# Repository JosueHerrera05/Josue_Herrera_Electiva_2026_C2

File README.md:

# Josue_Herrera_Electica_2026_C2
Repositorio Electíva Diseño Mecatrónico 2026-C2 
# PLC4UNI - Modelo NIVARA GC1

**PLC4UNI** es un Controlador Lógico Programable (PLC) modular, de código abierto y diseño robusto, creado específicamente como una plataforma didáctica para la enseñanza de mecatrónica y automatización. 

Este proyecto permite a los estudiantes interactuar con circuitos industriales reales manteniendo la seguridad del núcleo de procesamiento mediante aislamiento optoacoplado. El sistema está basado en el microcontrolador ESP32-S3.

## ¿En qué consiste el proyecto?
El proyecto abarca todo el ciclo de desarrollo de producto (basado en la norma IEEE-830 STD), incluyendo:
*   **Diseño Electrónico:** Esquemáticos y placa de circuito impreso (PCB) con entradas aisladas (24V DC), salidas a transistores de potencia/relé y puertos analógicos protegidos.
*   **Diseño Mecánico:** Carcasas personalizadas (superior e inferior) optimizadas para manufactura local mediante impresión 3D.
*   **Firmware/Software:** Código base de control que opera mediante un *Scan Cycle* de lazo cerrado (menor a 10ms) para garantizar el determinismo en tiempo real durante las prácticas.

## Programas Utilizados
Para visualizar, editar o compilar los archivos de este repositorio, se utilizaron las siguientes herramientas:
*   **[KiCad](https://www.kicad.org/):** Para el diseño esquemático, enrutamiento de la PCB y visualización 3D electrónica (`.kicad_sch`, `.kicad_pcb`).
*   **[FreeCAD](https://www.freecadweb.org/):** Para el diseño mecánico y modelado tridimensional de las carcasas (`.FCStd`).
*   **[Arduino IDE](https://www.arduino.cc/en/software) / [PlatformIO](https://platformio.org/):** Entornos de desarrollo para la programación del firmware en C/C++.
*   **Git:** Para el control de versiones de todo el proyecto.

## ¿Qué necesitas descargar e instalar?
Para trabajar con este proyecto en tu propia máquina, sigue estos pasos:

### 1. Clonar el repositorio
```bash
git clone https://github.com/JosueHerrera05/Josue_Herrera_Electica_2026_C2.git
```

### 2. Software Requerido
*   Instala **KiCad** (versión 7 o superior recomendada) si deseas editar las pistas, modificar los esquemas eléctricos o ver los modelos 3D de la placa.
*   Instala **FreeCAD** si necesitas modificar el diseño del chasis para ajustarlo a tu impresora 3D.
*   Instala el entorno de programación de tu preferencia (**Arduino IDE** o VSCode + **PlatformIO**) para cargar programas al PLC.

### 3. Dependencias de Hardware (Drivers y Librerías)
*   **Controlador USB-Serial:** Descarga e instala los drivers CH340 o CP2102 (según el módulo puente utilizado en tu placa) para que tu PC reconozca el PLC al conectarlo por cable USB.
*   **Gestor de Tarjetas ESP32:** Si usas Arduino IDE, debes instalar el paquete de tarjetas de Espressif (*esp32 by Espressif Systems*) desde el Gestor de Tarjetas para poder compilar y subir código al procesador ESP32-S3-WROOM-1.

## Estructura del Repositorio
*   `/CAD/`: Archivos de diseño mecánico y modelado 3D para la carcasa (FreeCAD).
*   `/PLC Electiva/`: Archivos del proyecto electrónico (KiCad), incluyendo esquemáticos, footprints y PCB.
*   `/Documentacion/`: Ensayos, manuales, reglamentos de seguridad y el documento oficial de especificaciones de requisitos (IEEE-830).
*   `/PLC4UNI/`: Directorio que contiene datasheets, referencias y archivos complementarios para la manufactura.

## Autores
*   **Desarrollo, Programación y Diseño:** Josue Stalin Herrera Valdez
*   **Dirección de Proyecto:** Carlos Pichardo
*   **Institución:** Instituto Tecnológico de Las Américas (ITLA) - Tecnólogo en Mecatrónica

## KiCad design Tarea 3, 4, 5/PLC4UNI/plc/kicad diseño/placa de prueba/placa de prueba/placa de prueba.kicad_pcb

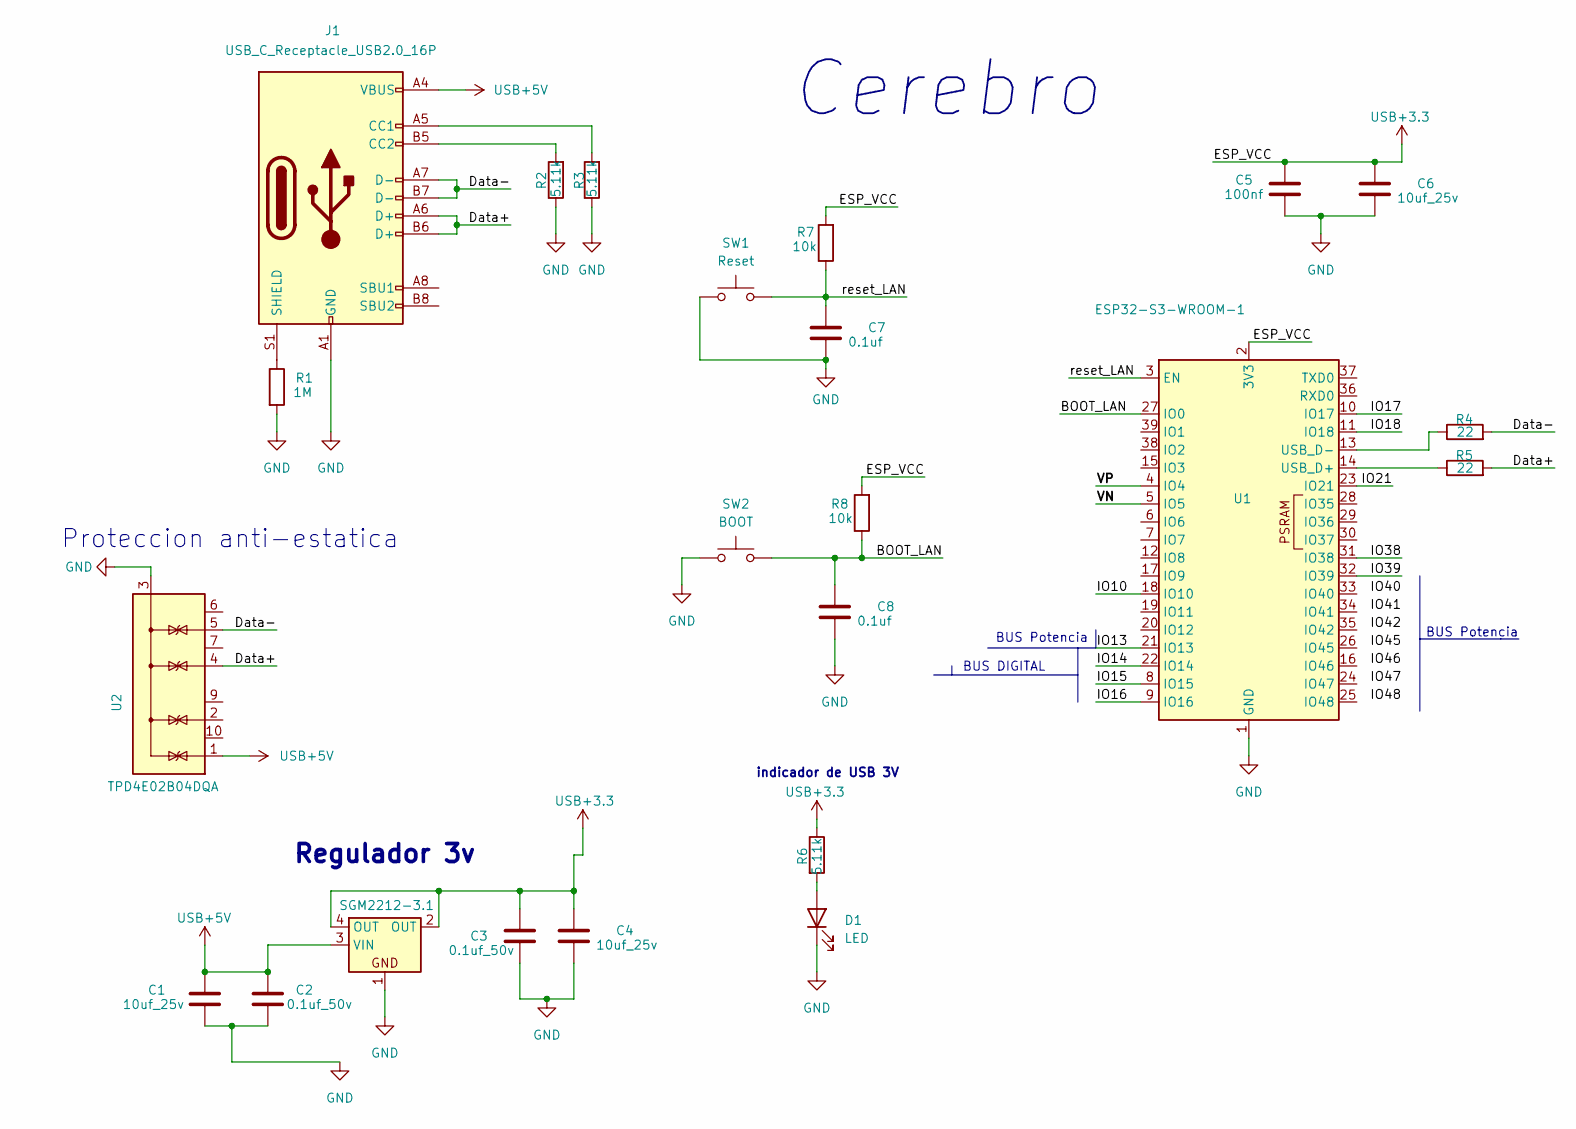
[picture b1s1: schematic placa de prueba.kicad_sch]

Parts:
C1, C4, C6: 10uf_25v; C_Disc_D4.7mm_W2.5mm_P5.00mm
C2, C3: 0.1uf_50v; C_Disc_D4.7mm_W2.5mm_P5.00mm
C5: 100nf; C_Disc_D4.7mm_W2.5mm_P5.00mm
C7, C8: 0.1uf; C_Disc_D4.7mm_W2.5mm_P5.00mm
D1: LED; LED_D1.8mm_W3.3mm_H2.4mm
J1: USB_C_Receptacle_USB2.0_16P; USB_C_Receptacle_GCT_USB4105-xx-A_16P_TopMnt_Horizontal
R1: 1M; R_Axial_DIN0414_L11.9mm_D4.5mm_P15.24mm_Horizontal
R2, R3, R6: 5.11k; R_Axial_DIN0414_L11.9mm_D4.5mm_P15.24mm_Horizontal
R4, R5: 22; R_Axial_DIN0414_L11.9mm_D4.5mm_P15.24mm_Horizontal
R7, R8: 10k; R_Axial_DIN0414_L11.9mm_D4.5mm_P15.24mm_Horizontal
SGM2212-3.1: SOT-223
SW1: Reset; SW_PUSH_6mm_H5mm
SW2: BOOT; SW_PUSH_6mm_H5mm
U1: ESP32-S3-WROOM-1
U2: TPD4E02B04DQA; USON-10_2.5x1.0mm_P0.5mm

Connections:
/BOOT_LAN: C8.1, R8.1, SW2.2, U1.27 (IO0)
/Data+: J1.A6 (D+), J1.B6 (D+), R5.2, U2.4 (IO3)
/Data-: J1.A7 (D-), J1.B7 (D-), R4.2, U2.5 (IO4)
/IO10: U1.18 (IO10)
/IO13: U1.21 (IO13)
/IO14: U1.22 (IO14)
/IO15: U1.8 (IO15)
/IO16: U1.9 (IO16)
/IO17: U1.10 (IO17)
/IO18: U1.11 (IO18)
/IO21: U1.23 (IO21)
/IO38: U1.31 (IO38)
/IO39: U1.32 (IO39)
/VN: U1.5 (IO5)
/VP: U1.4 (IO4)
/reset_LAN: C7.1, R7.1, SW1.2, U1.3 (EN)
GND: C1.2, C2.2, C3.2, C4.2, C5.2, C6.2, C7.2, C8.2, D1.1 (K), J1.A1 (GND), J1.A12 (GND), J1.B1 (GND), J1.B12 (GND), R1.2, R2.1, R3.1, SGM2212-3.1.1, SW1.1, SW2.1, U1.1 (GND), U1.40 (GND), U1.41 (GND), U2.3 (G), U2.8 (G)
unnamed: D1.2 (A), R6.2
unnamed: J1.A5 (CC1), R3.2
unnamed: J1.B5 (CC2), R2.2
unnamed: J1.S1 (SHIELD), R1.1
unnamed: R5.1, U1.14 (USB_D+)
unnamed: R4.1, U1.13 (USB_D-)
USB+3.3: C3.1, C4.1, C5.1, C6.1, R6.1, R7.2, R8.2, SGM2212-3.1.2 (OUT), SGM2212-3.1.4 (OUT), U1.2 (3V3)
USB+5V: C1.1, C2.1, J1.A4 (VBUS), J1.A9 (VBUS), J1.B4 (VBUS), J1.B9 (VBUS), SGM2212-3.1.3 (VIN), U2.1 (IO1)

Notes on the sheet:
Proteccion anti-estatica
BUS DIGITAL
BUS Potencia
Cerebro
indicador de USB 3V
Regulador 3v

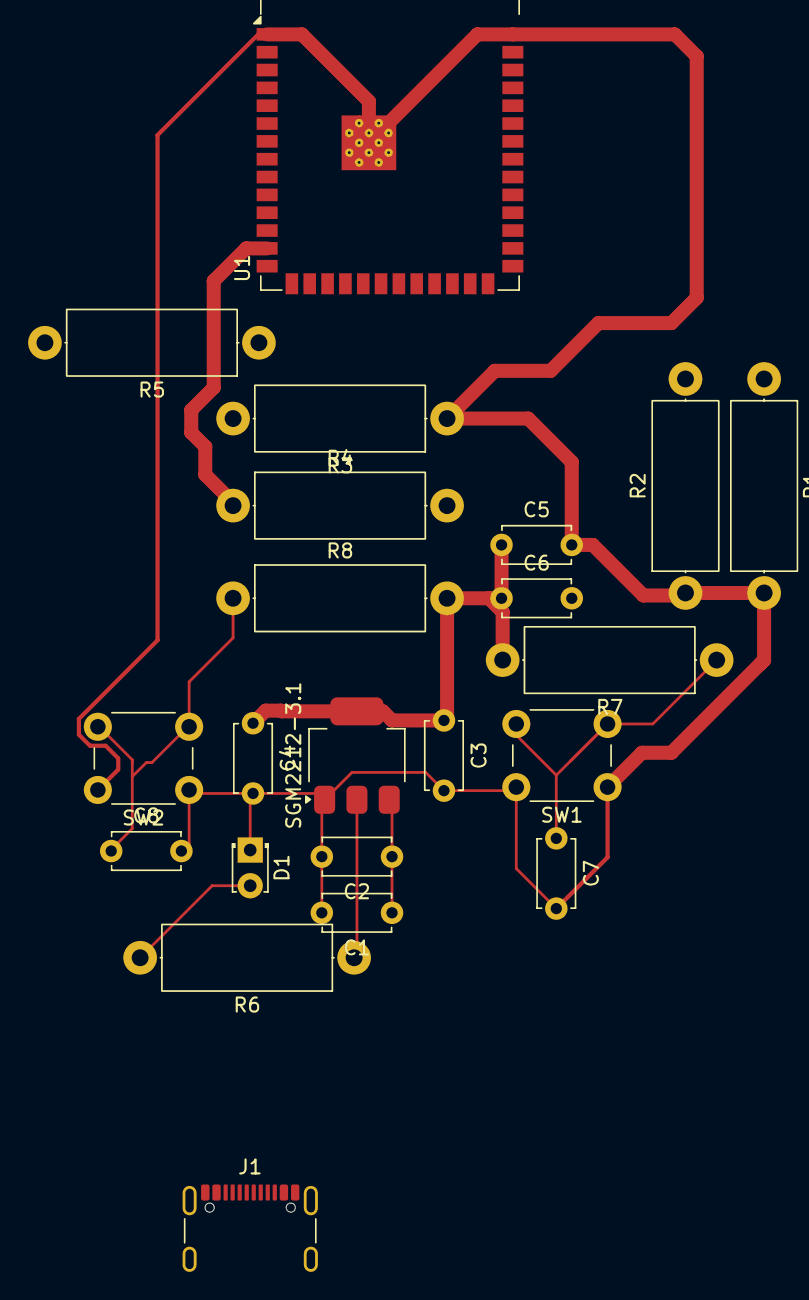
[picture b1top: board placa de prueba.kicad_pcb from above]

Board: 2 copper layers, 22 parts (0 on the bottom side), 13 nets.

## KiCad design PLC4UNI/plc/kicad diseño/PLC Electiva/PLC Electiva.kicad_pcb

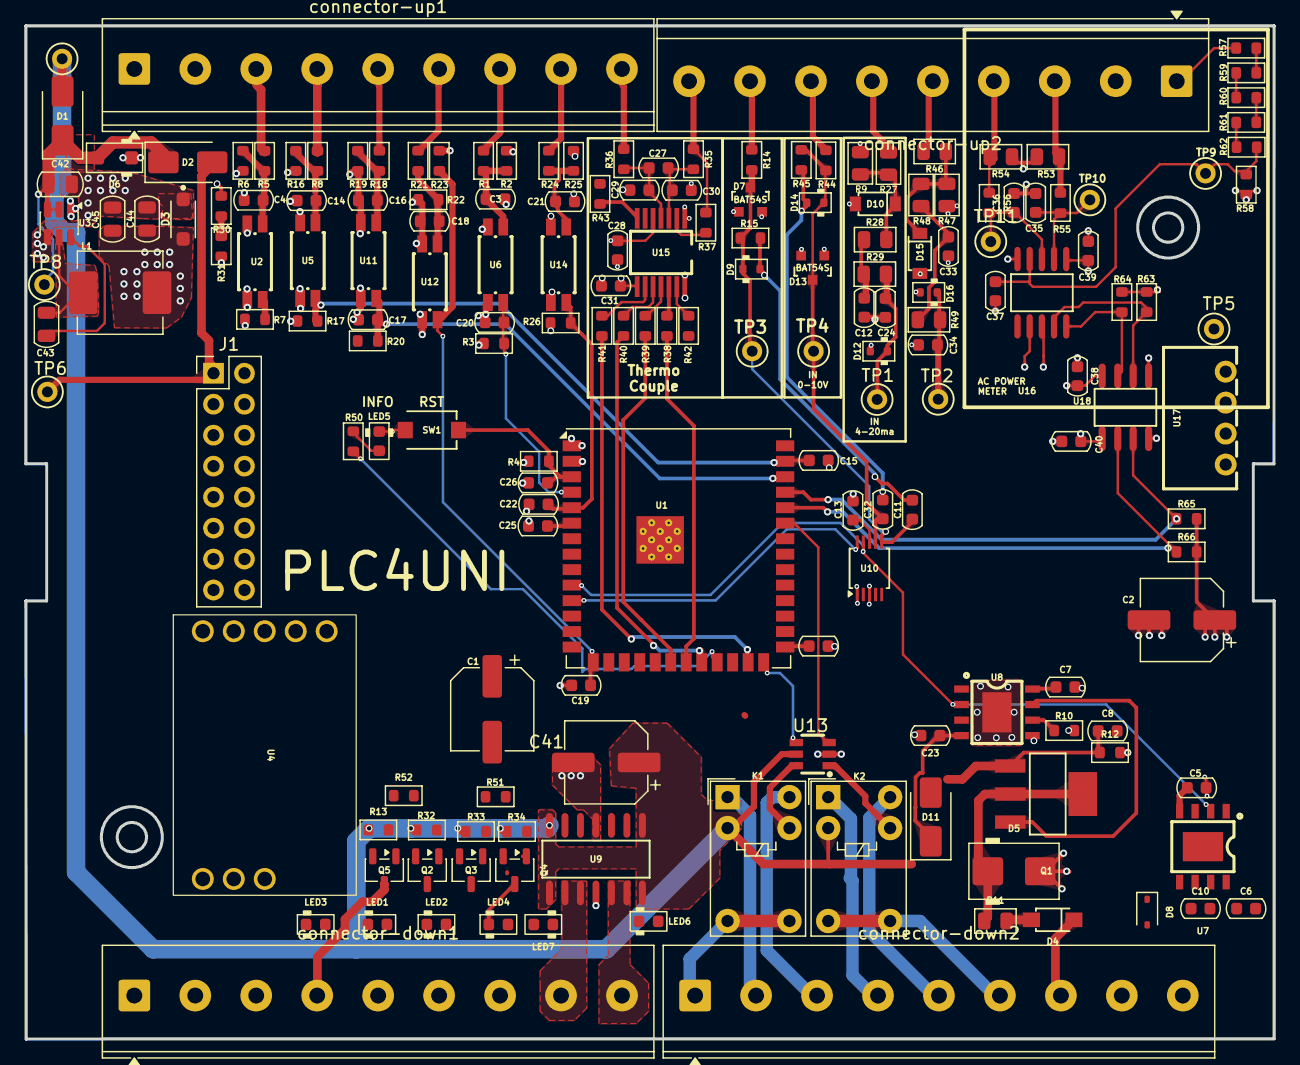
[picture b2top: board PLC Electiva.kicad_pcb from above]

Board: 2 copper layers, 102.4 x 83.1 mm, 177 parts (0 on the bottom side), 96 nets.

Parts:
C1, C2, C41: 47UF; CP_Elec_6.3x7.7
C3, C4, C14, C16, C18, C21: 2.2NF; C_0603_1608Metric
C5, C6, C7, C23: C_0603; C_0603_1608Metric
C8, C26: 1uF; C_0603_1608Metric
C9, C15, C17, C19, C20, C22: 1NF; C_0603_1608Metric
C10: 100nF; C_0603_1608Metric
C11, C12, C13, C28, C31, C32, C33, C38, C39, C40: 100NF; C_0603_1608Metric
C24, C34: 47PF; C_0603_1608Metric
C25: 100nf; C_0603_1608Metric
C27, C29, C30: 0.01UF; C_0603_1608Metric
C35, C36: 33NF; C_0603_1608Metric
C37: 68NF; C_0603_1608Metric
C42: 10uF; C_0805_2012Metric
C43: 100NF; C_0805_2012Metric
C44, C45: 22uF; C_0805_2012Metric
D1, D2: SS14; D_SMA
D3: SMF3.3; SMF3.3_SODFL3718X108N
D4: DSK120_C22466355; SOD-123FL_L2.7-W1.8-LS3.8-RD
D5: SMBJ28A; D_SMB
D6: SMF24CA; D_SOD-123F
D7, D13: BAT54S; SOT23-3_PO132
D8: SD12_SOD323; D_SOD-323
D9, D12, D14, D16: PESD5Z3.3; D_SOD-523
D10, D15: 1N5819HW-7-F; SOD-123_L2.7-W1.6-LS3.7-RD
D11: SMAJ12A; D_SMA
J1: Conn_02x08_Odd_Even; PinHeader_2x08_P2.54mm_Vertical
K1, K2: G5V-1; Relay_SPDT_Omron_G5V-1
L1: 10uH; L_APV_APH0630
LED1, LED2, LED3, LED4, LED5, LED6, LED7: LED_0603_Red; LED_0603_1608Metric
Q1: NCE60P04R; SOT-223-3_L6.5-W3.4-P2.30-LS7.0-BR
Q2, Q3, Q4, Q5: ZXMS6004FFQTA; SOT-23-3
R1, R5, R8, R18, R21, R24: 3.6K; R_0603_1608Metric
R2, R6, R16, R19, R22, R25: 3.3K; R_0603_1608Metric
R3, R4, R7, R17, R20, R23, R26: 22K; R_0603_1608Metric
R9, R47: 120R; R_0805_2012Metric
R10, R13, R30, R31, R32, R33, R34, R51, R52: R_0603; R_0603_1608Metric
R11: 15R; R_0805_2012Metric
R12: 470K; R_0603_1608Metric
R14, R44, R50: 2.2K; R_0603_1608Metric
R15, R45: 1.05K; R_0603_1608Metric
R27, R46: 49.9R; R_0805_2012Metric
R28, R48: 47K; R_0805_2012Metric
R29, R49: 100K; R_0805_2012Metric
R35, R36: 0R; R_0603_1608Metric
R37: 20K; R_0603_1608Metric
R38, R39, R40, R41, R42, R43: 150; R_0603_1608Metric
R53, R54: 0.51; R_0805_2012Metric
R55, R56: 1K; R_0603_1608Metric
R57, R59, R60, R61, R62: 390K; R_0603_1608Metric
R58: 510; R_0603_1608Metric
R63, R64, R65, R66: 4.7K; R_0603_1608Metric
SW1: TS-1088-AR02016; SW-SMD_L3.9-W3.0-P4.45
TP1, TP2, TP3, TP4, TP5, TP6, TP7, TP8, TP9, TP10, TP11: TestPoint_Hole1; TestPoint_WireHole
U1: ESP32-S3-WROOM-1; ESP32-S3-WROOM-1U
U2, U5, U6, U11, U12, U14: AT3H4B-CUH-S; SSOP-4_L2.7-W4.6-P1.27-LS7.0-TL
U3: AP63203WU; TSOT-23-6
U4: RS485-PROTECT; RS-485-PROTECT
U7: GP8211S-TC50-EW; ESOP-8_L4.9-W3.9-P1.27-LS6.0-BL-EP
U8: GP8302-TC50-EW; ESOP-8_L4.9-W3.9-P1.27-LS6.0-BL-EP
U9: BTS723GWXUMA1; SOIC-14_L8.7-W3.9-P1.27-LS6.0-BL
U10: ADS1115IDGS; TSSOP-10_3x3mm_P0.5mm
U13: LK1802; SOT-23-6_L2.9-W1.6-P0.95-LS2.8-BR
U15: MAX31856MUD+; TSSOP-14_L5.0-W4.4-P0.65-LS6.4-BL
U16: BL0942; SSOP-10_L4.9-W3.9-P1.00-LS6.0-BL
U17: B0303S-1WR3_C7465185; PWRM-TH_BXXXXS-1WR3
U18: ISO7021DR; SOIC-8_L4.9-W3.9-P1.27-LS6.0-BL
connector-down1, connector-down2: Screw_Terminal_9_P5.00mm; TerminalBlock_Phoenix_PT-1,5-9-5.0-H_1x09_P5.00mm_Horizontal
connector-up1, connector-up2: Screw_Terminal_9_P5.00mm; TerminalBlock_Phoenix_PT-1,5-9-5.0-H_1x09_P5.00mm_Horizontal

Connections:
+3.3V: C1.1, C2.1, C13.1, C28.1, C31.1, C40.2, C44.1, C45.1, D3.A, D7.2 (cathode), D13.2 (cathode), J1.2, L1.2, R3.2, R4.2, R7.2, R17.2, R20.2, R23.2, R26.2, R65.2, R66.2, U1.2 (3V3), U3.1 (FB), U4.1 (VCC), U9.11 (SPU), U10.8 (VDD), U15.5 (AVDD), U15.8 (DVDD), U17.2 (+Vin), U18.1 (VCC1)
+5V: D2.2 (A), J1.1, TP6.1 (1_1)
+24V: C4.2, C5.1, C14.2, C16.2, C18.2, C23.1, C41.1, D1.2 (A), D11.1 (A1), K1.2, K2.2, R6.1, R13.1, R16.1, R19.1, R22.1, R30.1, R32.1, R33.1, R34.1, TP7.1 (1_1), U2.2, U5.2, U7.4 (VCC), U8.4 (VCC), U9.1 (VBB), U9.7 (VBB), U9.8 (VBB), U9.14 (VBB), U11.2, U12.2, U13.5 (COM), connector-up1.9
/PowerSupply/sw: C43.2, L1.1, U3.5 (SW)
/PowerSupply/vdc_in: C42.1, D1.1 (K), D2.1 (K), D6.2 (A), TP8.1 (1_1), U3.2 (EN), U3.3 (IN)
/control/CON-IN_CT_N: R54.2, R56.1
/control/CON-IN_CT_P: R53.1, R55.1
/control/CON_IN_TC-: R35.1, R37.1
/control/CON_OUT_0-10V: C10.1, D8.2 (A2), U7.6 (VOUT)
/control/CON_OUT_NPN1: LED3.1 (K), Q5.3 (D)
/control/CON_OUT_NPN2: LED1.1 (K), Q2.3 (D)
/control/CON_OUT_NPN3: LED2.1 (K), Q3.3 (D)
/control/CON_OUT_NPN4: LED4.1 (K), Q4.3 (D)
/control/CON_OUT_PNP1: R51.1, U9.9 (OUT2), U9.10 (OUT2)
/control/CON_OUT_PNP2: R52.1, U9.12 (OUT1), U9.13 (OUT1)
/control/CON_OUT_RLY1_COM: K1.5, K1.6
/control/CON_OUT_RLY2_COM: K2.5, K2.6
/control/EMRX: R66.1, U1.36 (RXD0), U18.2 (OUTA)
/control/EM_TX: R65.1, U1.37 (TXD0), U18.3 (INB)
/control/EN: C26.2, R4.1, SW1.1, U1.3 (EN)
/control/IN-0-10V1/COM: C32.2, D14.2 (A), R45.2
/control/IN-0-10V1/OUT3V: C32.1, D13.3 (AK), D14.1 (K), R44.2, R45.1, TP4.1 (1_1), U10.7 (AIN3)
/control/IN-0-10V/COM: C11.2, D9.2 (A), R15.2
/control/IN-0-10V/OUT3V: C11.1, D7.3 (AK), D9.1 (K), R14.2, R15.1, TP3.1 (1_1), U10.6 (AIN2)
/control/IN-4-20MA1/OUT: C34.1, D16.1 (K), R49.1, TP2.1 (1_1), U10.5 (AIN1)
/control/IN-4-20MA/OUT: C24.1, D12.1 (K), R29.1, TP1.1 (1_1), U10.4 (AIN0)
/control/IN_NPN1: C9.1, R7.1, U1.27 (IO0), U2.4
/control/IN_NPN2: C15.1, R17.1, U1.39 (IO1), U5.4
/control/IN_NPN3: C17.1, R20.1, U1.38 (IO2), U11.4
/control/IN_NPN4: C19.1, R23.1, U1.15 (IO3), U12.4
/control/IN_PNP1: C20.1, R3.1, U1.4 (IO4), U6.4
/control/IN_PNP2: C22.1, R26.1, U1.5 (IO5), U14.4
/control/IN_VDC_ADC: C25.1, R30.2, R31.1, U1.6 (IO6)
/control/LED_INFO: R50.2, U1.23 (IO21)
/control/OUT_NPN1: Q5.1 (IN), U1.31 (IO38)
/control/OUT_NPN2: Q2.1 (IN), U1.32 (IO39)
/control/OUT_NPN3: Q3.1 (IN), U1.33 (IO40)
/control/OUT_NPN4: Q4.1 (IN), U1.34 (IO41)
/control/OUT_PNP1: U1.16 (IO46), U9.2 (IN1)
/control/OUT_PNP2: U1.24 (IO47), U9.6 (IN2)
/control/OUT_RLY1: U1.35 (IO42), U13.3 (1B)
/control/OUT_RLY2: U1.26 (IO45), U13.4 (2B)
/control/TEMP_CS: R41.2, U1.25 (IO48)
/control/clk: R40.2, U1.22 (IO14)
/control/i2c_scl: U1.11 (IO18), U7.1 (SCLK), U8.1 (SLCK), U10.10 (SCL)
/control/i2c_sda: U1.10 (IO17), U7.2 (SDA), U8.2 (SDA), U10.9 (SDA)
/control/miso: R39.2, U1.20 (IO12)
/control/mosi: R38.2, U1.21 (IO13)
Earth: C35.1, C36.2, C37.1, C38.1, C39.1, R53.2, R54.1, R58.1, U16.5 (GND), U16.7 (SEL), U17.3 (-Vout), U18.5 (GND2), connector-up2.2
GND: C1.2, C2.2, C3.2, C5.2, C6.2, C7.2, C8.2, C9.2, C10.2, C12.2, C13.2, C15.2, C17.2, C19.2, C20.2, C21.2, C22.2, C23.2, C24.2, C25.2, C26.1, C28.2, C29.2, C30.2, C31.2, C33.2, C34.2, C40.1, C41.2, C42.2, C44.2, C45.2, D3.C, D5.2 (A), D6.1 (K), D7.1 (Anode), D8.1 (A1), D10.2 (A), D12.2 (A), D13.1 (Anode), D15.2 (A), D16.2 (A), J1.15, J1.16, LED5.1 (K), LED6.1 (K), LED7.1 (K), Q2.2 (OUT), Q3.2 (OUT), Q4.2 (OUT), Q5.2 (OUT), R2.1, R9.1, R10.2, R12.2, R25.1, R31.2, R47.1, SW1.2, U1.1 (GND), U1.40 (GND), U1.41 (GND), U2.3, U3.4 (GND), U4.2 (GND), U5.3, U6.2, U6.3, U7.5 (GND), U7.9 (EP), U8.5 (GND), U8.9 (EP), U9.4 (GND), U10.1 (ADDR), U10.3 (GND), U11.3, U12.3, U13.2 (E), U14.2, U14.3, U15.1 (AGND), U15.14 (DGND), U17.1 (-Vin), U18.4 (GND1), connector-down2.9, connector-up1.8
unnamed: C3.1, R1.2, R2.2, U6.1
unnamed: C4.1, R5.2, R6.2, U2.1
unnamed: C12.1, R28.1, R29.2
unnamed: C14.1, R8.2, R16.2, U5.1
unnamed: C16.1, R18.2, R19.2, U11.1
unnamed: C18.1, R21.2, R22.2, U12.1
unnamed: C21.1, R24.2, R25.2, U14.1
unnamed: C33.1, R48.1, R49.2
unnamed: D4.2 (A), R11.2
unnamed: D5.1 (K), Q1.2, Q1.4, R11.1
unnamed: D10.1 (K), R9.2, R27.1, R28.2
unnamed: C8.1, D11.2 (A2), Q1.1, R12.1
unnamed: D15.1 (K), R46.1, R47.2, R48.2
unnamed: LED1.2 (A), R32.2
unnamed: LED2.2 (A), R33.2
unnamed: LED3.2 (A), R13.2
unnamed: LED4.2 (A), R34.2
unnamed: LED5.2 (A), R50.1
unnamed: LED6.2 (A), R51.2
unnamed: LED7.2 (A), R52.2
unnamed: R57.2, R59.1
unnamed: R59.2, R60.1
unnamed: R60.2, R61.1
unnamed: R61.2, R62.1
unnamed: C43.1, U3.6 (BST)
unnamed: C6.1, U7.8 (V5V)
unnamed: Q1.3, U8.7 (IOUT)
unnamed: R10.1, U8.6 (SET)
unnamed: C7.1, U8.8 (V5V)
unnamed: K2.9, U13.1 (1C)
unnamed: K1.9, U13.6 (2C)
unnamed: R37.2, U15.2 (BIAS)
unnamed: R40.1, U15.10 (SCK)
unnamed: R38.1, U15.12 (SDI)
unnamed: R39.1, U15.11 (SDO)
unnamed: C27.2, C29.1, R36.2, U15.4 (T+)
unnamed: C27.1, C30.1, R35.2, U15.3 (T-)
unnamed: R41.1, U15.9 (~CS)
unnamed: R43.1, U15.7 (~DRDY)
unnamed: R42.1, U15.13 (~FAULT)
unnamed: C36.1, R56.2, TP11.1 (1_1), U16.3 (IN)
unnamed: C35.2, R55.2, TP10.1 (1_1), U16.2 (IP)
unnamed: R63.1, U16.9 (RX/SDI), U18.6 (OUTB)
unnamed: R64.1, U16.10 (TX/SDO), U18.7 (INA)
unnamed: C37.2, R58.2, R62.2, TP9.1 (1_1), U16.4 (VP)
VCC: C38.2, C39.2, R63.2, R64.2, TP5.1 (1_1), U16.1 (VDD), U16.8 (SCLK_BPS), U17.4 (+Vout), U18.8 (VCC2)

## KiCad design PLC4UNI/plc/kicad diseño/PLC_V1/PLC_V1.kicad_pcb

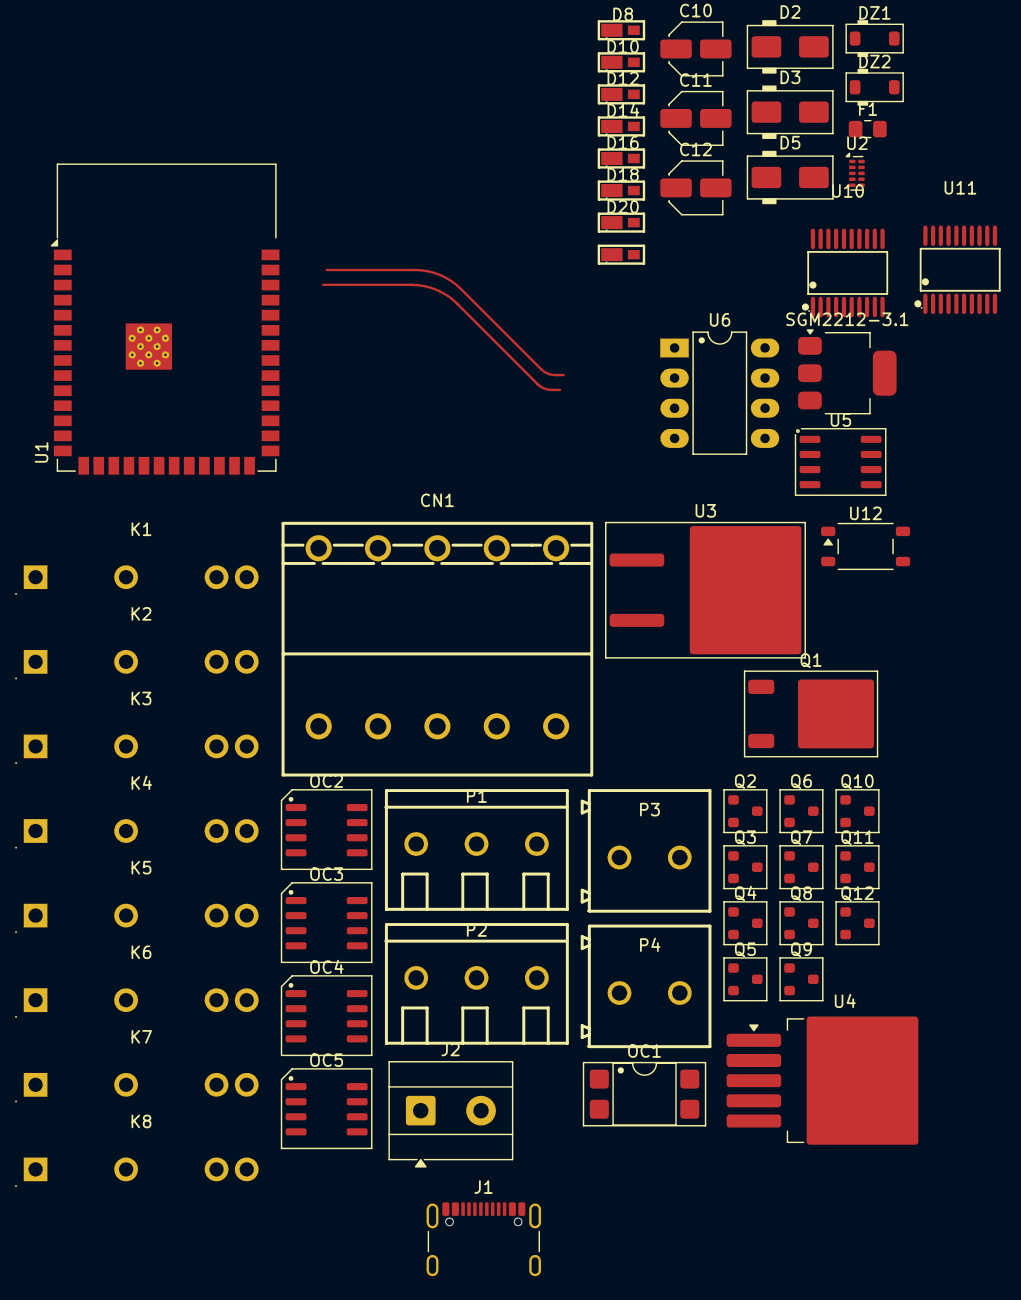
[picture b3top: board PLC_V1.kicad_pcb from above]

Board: 2 copper layers, 59 parts (0 on the bottom side), 47 nets.

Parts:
C10: 470uf; C_Elec_4x5.4
C11: 47uf; C_Elec_4x5.4
C12: 220uf; C_Elec_4x5.4
CN1: KFM736-5.0-5P; CONN-TH_5P-P5.00_KFM736-5.0-5P
D2, D5: SS14; D_SMA
D3: B330A; D_SMA
D6, D8, D10, D12, D14, D16, D18, D20: RR1VWM6STFTR; PMDE_L2.2-W1.3-LS2.5-RD
DZ1, DZ2: MMSZ3V6; D_SOD-123
F1: Fuse_Small 1A; Fuse_0805_2012Metric_Pad1.15x1.40mm_HandSolder
J1: USB_C_Receptacle_USB2.0_16P; USB_C_Receptacle_GCT_USB4105-xx-A_16P_TopMnt_Horizontal
J2: 24; TerminalBlock_MetzConnect_Type101_RT01602HBWC_1x02_P5.08mm_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
K1, K2, K3, K4, K5, K6, K7, K8: HF49FD/012-1H12G; RELAY-TH_HF49FD-012-1H12G
OC1: PC817; DIP-4_W7.62mm_SMDSocket_SmallPads
OC2, OC3, OC4, OC5: ILD207T; SO-8_3.9x6.2mm_P1.27mm
P1, P2: WJ500V-5.08-3P-14-00A; CONN-TH_3P-P5.00_WJ500V-5.08-3P
P3, P4: WJ500V-5.08-2P-14-00A; CONN-TH_2P-P5.00_WJ500V-5.08-2P
Q1: FQD11P06; TO-252-2
Q2, Q3, Q4, Q5, Q6, Q7, Q8, Q9, Q10, Q11, Q12: PMBT3904; SOT-23
SGM2212-3.1: SOT-223
U1: ESP32-S3-WROOM-1
U2: TPD4E02B04DQA; USON-10_2.5x1.0mm_P0.5mm
U3: L7812CD2T; TO-263-2
U4: LM2576HVS-3.3; TO-263-5_TabPin3
U5: LM358M; SO-8_3.9x4.9mm_P1.27mm
U6: LM358N; DIP-8_W7.62mm_LongPads
U10, U11: 74HC541TS; TSSOP-20_L6.5-W4.4-P0.65-LS6.4-BL
U12: TLP127; Toshiba_SOIC-4-6_4.4x3.6mm_P1.27mm

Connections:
+3.3VCC: C11.1, OC1.4, Q1.2 (D), U1.2 (3V3), U4.4 (FB), U5.2 (-), U10.20 (VCC), U11.20 (VCC), U12.6
+12V: C12.1, U3.3 (OUT), U6.8 (V+)
+24.V: F1.1, J2.2
+24V_F: C10.1, D2.1 (K), D6.1 (C), D8.1 (C), D10.1 (C), D12.1 (C), D14.1 (C), D16.1 (C), D18.1 (C), D20.1 (C), K1.4, K2.4, K3.4, K4.4, K5.4, K6.4, K7.4, K8.4, U3.1 (IN), U4.1 (VIN), U5.4 (V-)
/0E1_IN: Q2.3 (C), U10.1 (~OE1)
/COM: K1.2, K2.2, K3.2, K4.2, K5.2, K6.2, K7.2, K8.2, P3.2, P4.2
/Data+: J1.A6 (D+), J1.B6 (D+), U2.4 (IO3)
/Data-: J1.A7 (D-), J1.B7 (D-), U2.5 (IO4)
/IO13: U1.21 (IO13), U11.9 (A8)
/IO14: U1.22 (IO14), U10.18 (Y1)
/IO15: U1.8 (IO15), U10.17 (Y2)
/IO16: U1.9 (IO16), U10.16 (Y3)
/IO17: U1.10 (IO17), U10.15 (Y4)
/IO18: U1.11 (IO18), U10.14 (Y5)
/IO21: U1.23 (IO21), U10.13 (Y6)
/IO38: U1.31 (IO38), U10.12 (Y7)
/IO39: U1.32 (IO39), U10.11 (Y8)
/OE1_OUT: Q3.3 (C), U11.1 (~OE1)
/OE2_OUT: Q4.3 (C), U11.19 (~OE2)
/Q0.0: K1.1, P4.1
/Q0.1: K2.1, P1.3
/Q0.2: K3.1, P1.2
/Q0.3: K4.1, P1.1
/Q0.4: K5.1, P3.1
/Q0.5: K6.1, P2.3
/Q0.6: K7.1, P2.2
/Q0.7: K8.1, P2.1
/RL1: D6.2 (A), K1.3, Q5.3 (C)
/RL2: D8.2 (A), K2.3, Q6.3 (C)
/RL3: D10.2 (A), K3.3, Q7.3 (C)
/RL4: D12.2 (A), K4.3, Q8.3 (C)
/RL5: D14.2 (A), K5.3, Q9.3 (C)
/RL6: D16.2 (A), K6.3, Q10.3 (C)
/RL7: D18.2 (A), K7.3, Q11.3 (C)
/RL8: D20.2 (A), K8.3, Q12.3 (C)
/VN: DZ2.1 (K), U1.5 (IO5)
/VP: DZ1.1 (K), U1.4 (IO4)
/k_IN: D5.2 (A), OC2.2, OC2.4, OC3.2, OC3.4, OC4.2, OC4.4, OC5.2, OC5.4
GND: C10.2, C11.2, C12.2, D3.2 (A), DZ1.2 (A), DZ2.2 (A), J1.A1 (GND), J1.A12 (GND), J1.B1 (GND), J1.B12 (GND), J2.1, OC1.2, OC2.5, OC2.7, OC3.5, OC3.7, OC4.5, OC4.7, OC5.7, Q2.2 (E), Q3.2 (E), Q4.2 (E), Q5.2 (E), Q6.2 (E), Q7.2 (E), Q8.2 (E), Q9.2 (E), Q10.2 (E), Q11.2 (E), Q12.2 (E), SGM2212-3.1.1, U1.1 (GND), U1.40 (GND), U1.41 (GND), U2.3 (G), U2.8 (G), U3.2, U4.3 (GND), U4.5 (~ON/OFF), U5.8 (V+), U6.4 (V-), U10.10 (GND), U10.19 (~OE2), U11.10 (GND), U12.3
unnamed: D2.2 (A), F1.2
unnamed: D3.1 (K), U4.2 (OUT)
unnamed: CN1.5, CN1.6, D5.1 (K)
unnamed: OC1.3, Q1.1 (G)
unnamed: U6.1, U6.2 (-)
unnamed: U6.6 (-), U6.7
USB+3.3: Q1.3 (S), SGM2212-3.1.2 (OUT), SGM2212-3.1.4 (OUT)
USB+5V: J1.A4 (VBUS), J1.A9 (VBUS), J1.B4 (VBUS), J1.B9 (VBUS), SGM2212-3.1.3 (VIN), U2.1 (IO1)

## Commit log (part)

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2026-06-08 Añadiendo tarea 1
2026-06-11 Añadiendo el diseño de las PCB
2026-06-11 Simplemente añadí un archívo innecesario al gitignore
2026-06-11 De nuevo el gitignore porque no se habia quitado el archivo
2026-06-11 Añadiendo la plantilla de la documentación (no completada, se actualizará)
